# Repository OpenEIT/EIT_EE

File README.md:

# Spectra PDF

The schematic for the 32 electrode EIT system is called Spectra.pdf and is contained in the top level directory. Please let me know if you think it should have any modifications. 

# Eagle_EIT

Note: the following design is an older design for an 8 electrode system. I have a newer better system which was designed in Altium which I'll put up here as soon as crowd supply campaign finalized. In the meantime I'd love it if you wanted to join the mailing list! 

https://www.crowdsupply.com/mindseye-biomedical/spectra

## EIT PCB design in Eagle CAD

Electrical Impedance Tomography is a new way to image conductivity changes inside any mostly liquid medium - such as the human body. It's attractive as it doesn't use ionizing radiation like the X-rays used in a CATSCAN, and could be relatively cheap to mass produce. 

This project is an example of a working system from PCB to firmware to reconstruction algorithm. Further work could certainly improve the resolution, but for now we have functionality in all sub sections. 

This is everything required for the basic 8 electrode design to work. Photo of the assembled PCB included. 

The design is based on the ADuCM350 which has a dedicated high precision front end with 16 bit resolution 160 kSPS data speed.The front end also performs a DFT at the rate of 13.8ms per calculation. This leads to a high performance minimal noise set up, excellent for both R&D or educational purposes. 

In the not too distant future kits may be available with a smaller version of the PCB mounted in a box, an electrode harness for mounting to the body, and all cables required to run. 

This combination would be an excellent educational tool for those researching this area, as it allows you to try most of the reconstruction algorithms or come up with your own and quantify any improvements in results. 

It's the same technique as is used in CATSCAN's, except the current running through the body instead of dangerous ionizing radiation of X-Rays. 

Improvements are welcome to this design. To increase resolution you could make a rotational version which is time resolution limited, or simply add more electrodes and re-compute the reconstruction that way. Another intended improvement is to move to tetrapolar differential electrodes set up. If you'd like to collaborate just pull the repository or email contact@mindseyebiomedical.com

We'd love to hear how you are using this! 

## New Board Design 

We have a newer better board design which is uploaded and called Spectra.pdf. Check it out. 

## Future Plans 

Are hatching! Join the technical discussion list to discuss further at openeit.github.io 

## License 

The Creative Commons Attribution-NonCommercial-ShareAlike 4.0 International License seems to fit best with this project. Check out the human readable summary here: 

<br />This work is licensed under a <a rel="license" href="http://creativecommons.org/licenses/by-nc-sa/4.0/">Creative Commons Attribution-NonCommercial-ShareAlike 4.0 International License</a>.

If you'd like to make a derivative of this project in a commercial setting, we'd love a payment so that we can afford to spend time both maintaining this project and making more projects like this one. If this hybrid open source model works, it would enable open source projects to receive some funding, making the global commons stronger to benefit everyone.

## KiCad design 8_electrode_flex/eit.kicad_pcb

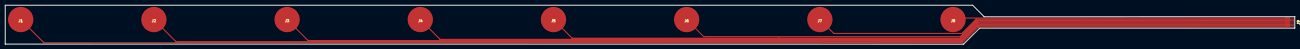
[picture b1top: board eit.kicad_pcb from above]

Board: 2 copper layers, 509.4 x 15.4 mm, 9 parts (0 on the bottom side), 8 nets.

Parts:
J1, J2, J3, J4, J5, J6, J7, J8: TEST_1P; electrode10mm
J9: Conn_01x08; fpc-0.5mm-8p

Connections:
unnamed: J1.1, J9.1
unnamed: J2.1, J9.2
unnamed: J3.1, J9.3
unnamed: J4.1, J9.4
unnamed: J5.1, J9.5
unnamed: J6.1, J9.6
unnamed: J7.1, J9.7
unnamed: J8.1, J9.8

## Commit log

2017-11-22 8 electrode EIT system
2017-11-22 Create LICENSE
2017-11-27 readme improvements
2017-11-27 readme improvement
2018-01-17 EIT schematic added
2018-07-29 CC BY-NC-SA 4.0
    See https://creativecommons.org/licenses/by-nc-sa/4.0/ for details.
2018-10-19 This is my first test.
2019-01-18 readme changes
2019-01-18 readme update
2019-04-08 8 electrode flex gerbers added
2021-01-27 Update README.md
    updated readme to included note on spectra schematic.
